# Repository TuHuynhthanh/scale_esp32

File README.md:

# scale_esp32
esp32 read information from electronic scale.
- USB HID CP2110
- USB COM debug ESP32 via terminal

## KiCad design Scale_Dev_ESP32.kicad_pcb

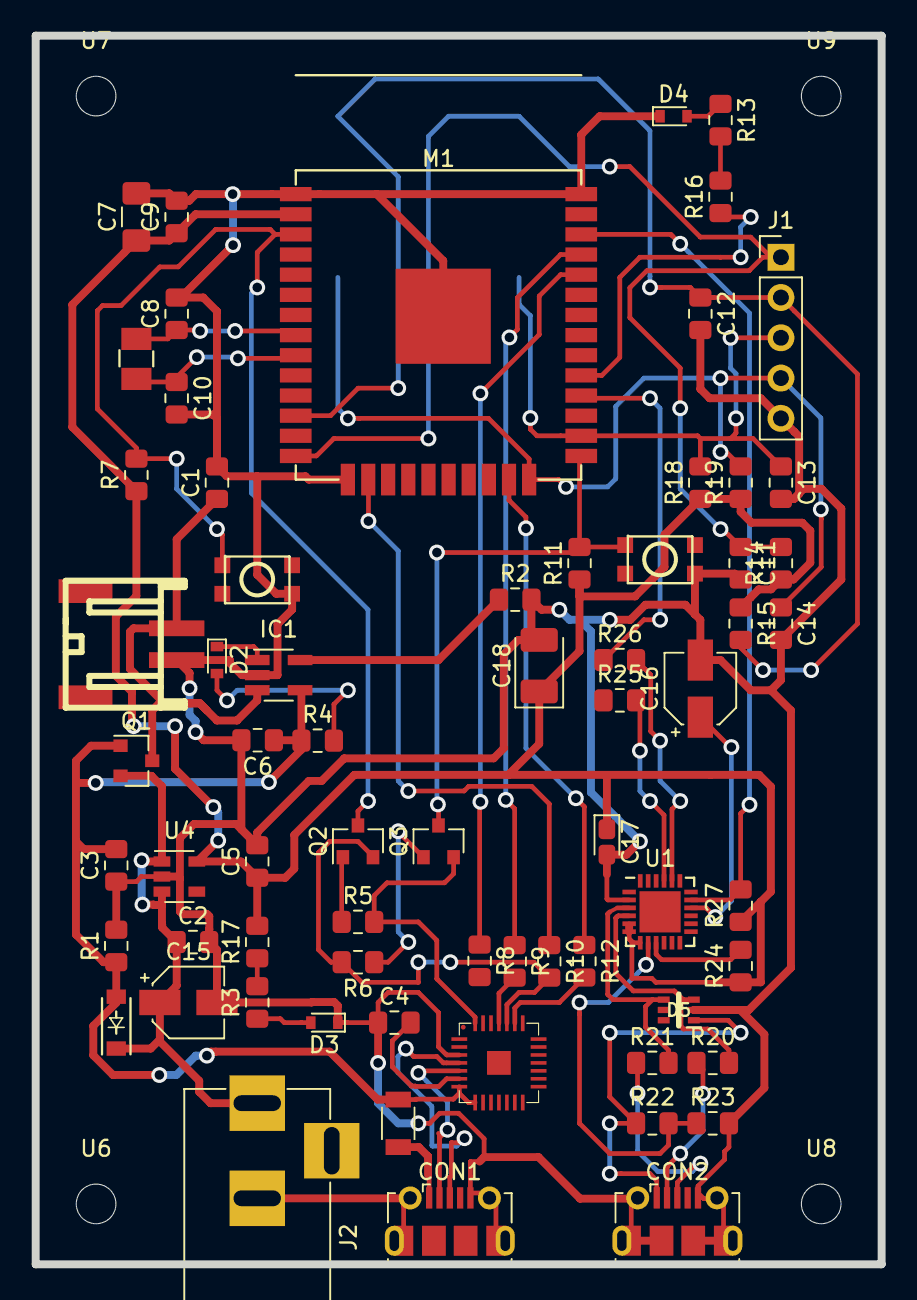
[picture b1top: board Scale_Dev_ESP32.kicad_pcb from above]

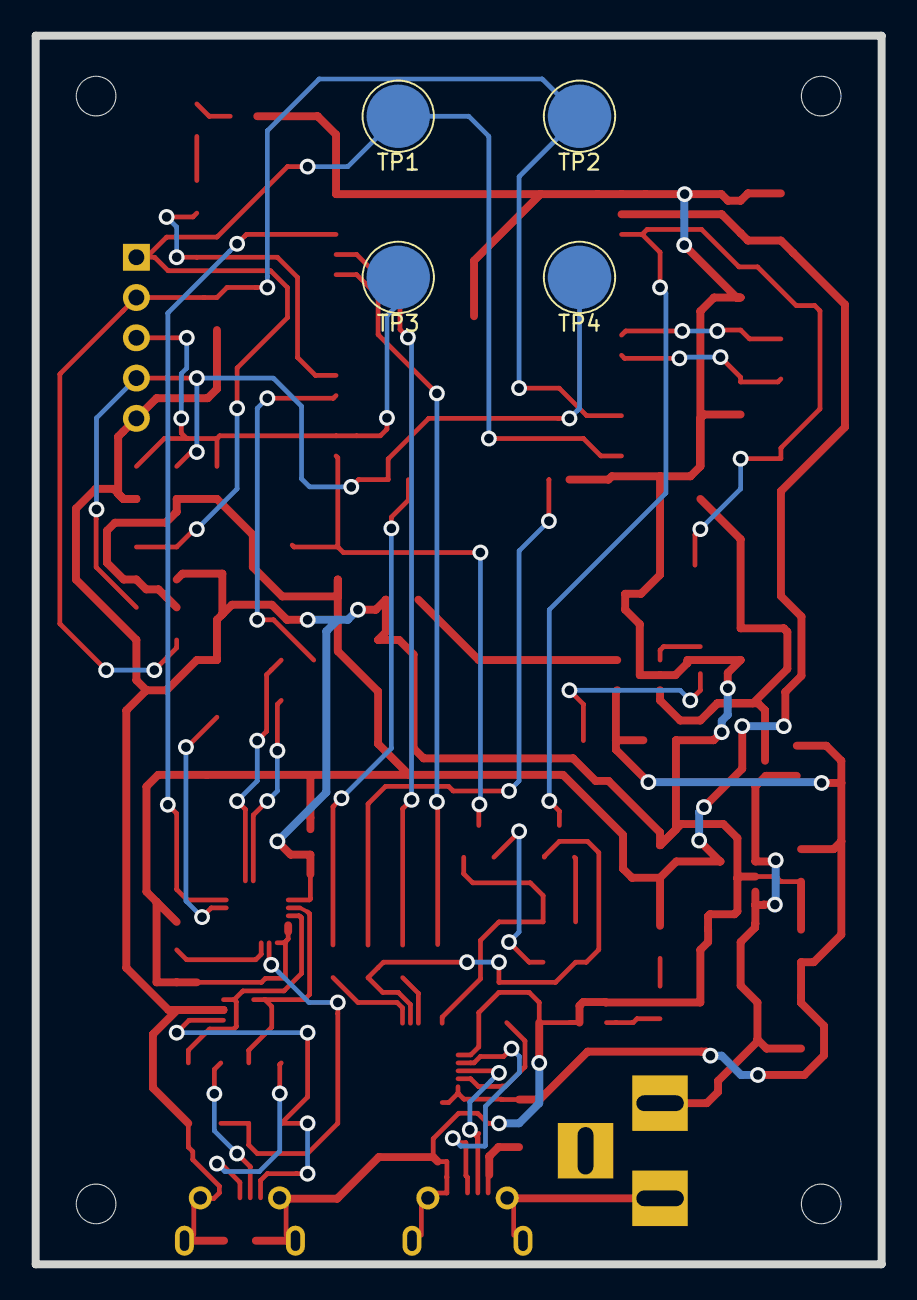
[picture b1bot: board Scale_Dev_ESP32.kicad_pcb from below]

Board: 2 copper layers, 53.3 x 77.5 mm, 75 parts (4 on the bottom side), 47 nets.

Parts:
C1, C6: 4.7uF; C_0805_2012Metric_Pad1.15x1.40mm_HandSolder
C2: 1uF; C_0805_2012Metric_Pad1.15x1.40mm_HandSolder
C3, C4: 0.1uF; C_0805_2012Metric_Pad1.15x1.40mm_HandSolder
C5: 2.2uF; C_0805_2012Metric_Pad1.15x1.40mm_HandSolder
C7: 100uF; C_1206_3216Metric_Pad1.42x1.75mm_HandSolder
C8, C10: 15pF; C_0805_2012Metric_Pad1.15x1.40mm_HandSolder
C9: 100nF; C_0805_2012Metric_Pad1.15x1.40mm_HandSolder
C11, C12, C13, C14: C; C_0805_2012Metric_Pad1.15x1.40mm_HandSolder
C15: 10uF; CP_Elec_4x3
C16: 4.7uF; CP_Elec_4x3
C17: 0.1uF; CP_EIA-1608-10_AVX-L_Pad1.25x1.05mm_HandSolder
C18: 1uF; CP_EIA-3528-12_Kemet-T_Pad1.50x2.35mm_HandSolder
CON1, CON2: USB_B_Micro; USB_Micro-B_Molex-105017-0001
D1: BAT20J; SOD-80_diode_1
D2: Yellow; D_0603
D3: LED; D_0603
D4: Blue; D_0603
D5: SMF05C; SC-70-6
F1: 500mA; Fuse_500mA
IC1: MCP73831; SOT-23-5_HandSoldering
J1: BUTTON; PinHeader_1x05_P2.54mm_Vertical
J2: Jack-DC; BARREL_JACK
M1: ESP-WROOM-32; ESP-32S
P1: LIPO; JST_SMD
Q1: IRLML5203; SOT-23
Q2, Q3: S8050; SOT-23
R1: 100K; R_0805_2012Metric_Pad1.15x1.40mm_HandSolder
R2: 2K; R_0805_2012Metric_Pad1.15x1.40mm_HandSolder
R3, R4: 1K; R_0805_2012Metric_Pad1.15x1.40mm_HandSolder
R5, R6: 12K; R_0805_2012Metric_Pad1.15x1.40mm_HandSolder
R7, R11, R14, R18, R19: 10K; R_0805_2012Metric_Pad1.15x1.40mm_HandSolder
R8, R9, R10, R12, R16, R17: 0E; R_0805_2012Metric_Pad1.15x1.40mm_HandSolder
R13: 330E; R_0805_2012Metric_Pad1.15x1.40mm_HandSolder
R15: 10k; R_0805_2012Metric_Pad1.15x1.40mm_HandSolder
R20, R21, R25, R26: 22R; R_0805_2012Metric_Pad1.15x1.40mm_HandSolder
R22: 47K; R_0805_2012Metric_Pad1.15x1.40mm_HandSolder
R23: 24K; R_0805_2012Metric_Pad1.15x1.40mm_HandSolder
R24: 4K7; R_0805_2012Metric_Pad1.15x1.40mm_HandSolder
R27: R; R_0805_2012Metric_Pad1.15x1.40mm_HandSolder
SW1, SW2: SW_PUSH; smd_push2_New
TP1, TP2, TP3, TP4: TestPoint; TestPoint_Pad_D4.0mm
U1: CP2110; QFN-24-1EP_4x4mm_Pitch0.5mm
U4: AP2112K; SOT-23-5
U5: CP2102; cp2102_xl2
U6, U7, U8, U9: MountingHole; MountingHole_2.5mm
Y1: 32.768KHz RTC Crystal; SMD_RTC_Crstl

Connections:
+3V3: C5.1, C7.1, C9.1, C17.1, C18.1, M1.2, R7.1, R11.1, R14.1, R15.1, R17.2, R18.1, R19.1, R24.1, R27.1, U1.5, U1.6, U1.7, U4.5
+5V: C2.1, C15.1, D1.1, J2.1, Q1.2, U4.1, U4.3
+BATT: C1.1, IC1.3, P1.1, Q1.3
/BUT0: C11.1, J1.1, M1.14, R14.2, TP1.1
/BUT1: C12.1, J1.2, M1.12, R15.2, TP2.1
/BUT2: C13.1, J1.3, M1.26, R18.2, TP3.1
/BUT3: C14.1, J1.4, M1.24, R19.2, TP4.1
/CP2110_SUS: M1.36, R27.2, U1.17
/DTR: Q3.2, R5.2
/EN: M1.3, Q2.3, R7.2, SW1.1
/IO0: M1.25, Q3.3, R11.2, SW2.1
/IO5: M1.29, R16.1
/IO13: M1.16, R10.1
/IO15: M1.23, R12.1
/IO32: C8.1, M1.8, Y1.1
/IO33: C10.1, M1.9, Y1.2
/RTS: Q2.2, R6.2, R10.2, U5.24
/RXD0: M1.34, R8.1
/TXD0: M1.35, R9.1
/U2_TX: M1.28, R26.1
/USB_N: D5.3, R20.2, U1.4
/USB_P: D5.4, R21.2, U1.3
/VBUS: R22.2, R23.1, U1.8
GND: C1.2, C2.2, C3.1, C4.1, C5.2, C6.2, C7.2, C8.2, C9.2, C10.2, C11.2, C12.2, C13.2, C14.2, C15.2, C16.2, C17.2, C18.2, CON1.5, CON1.6, CON2.5, CON2.6, D3.1, D4.1, D5.2, IC1.2, J1.5, J2.2, M1.1, M1.15, M1.38, P1.2, R1.2, R2.2, R23.2, SW1.2, SW2.2, U1.2, U4.2, U5.3
unnamed: C4.2, U5.6
unnamed: C16.1, U1.16
unnamed: CON1.1, F1.2
unnamed: CON1.2, U5.5
unnamed: CON1.3, U5.4
unnamed: CON2.1, D5.1, R22.1
unnamed: CON2.2, R20.1
unnamed: CON2.3, R21.1
unnamed: D2.1, IC1.1
unnamed: D2.2, R4.2
unnamed: D3.2, R3.1
unnamed: D4.2, R13.1
unnamed: IC1.5, R2.1
unnamed: Q2.1, R5.1
unnamed: Q3.1, R6.1
unnamed: R9.2, U5.25
unnamed: R12.2, U5.23
unnamed: R13.2, R16.2
unnamed: R3.2, R17.1
unnamed: R24.2, U1.9
unnamed: R25.2, U1.21
unnamed: R26.2, U1.20
VCC: C3.2, C6.1, D1.2, F1.1, IC1.4, Q1.1, R1.1, R4.1, U5.7, U5.8

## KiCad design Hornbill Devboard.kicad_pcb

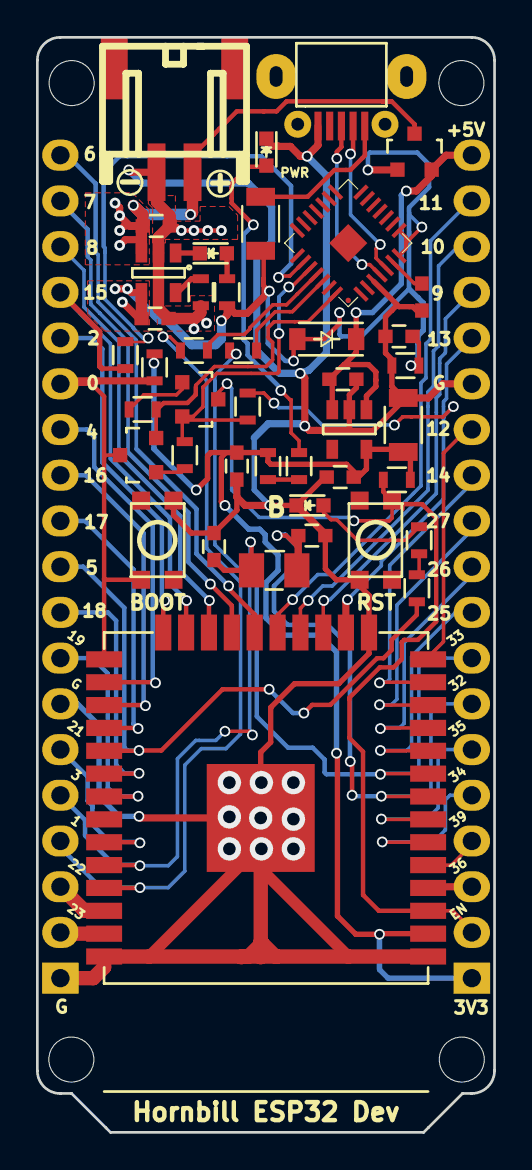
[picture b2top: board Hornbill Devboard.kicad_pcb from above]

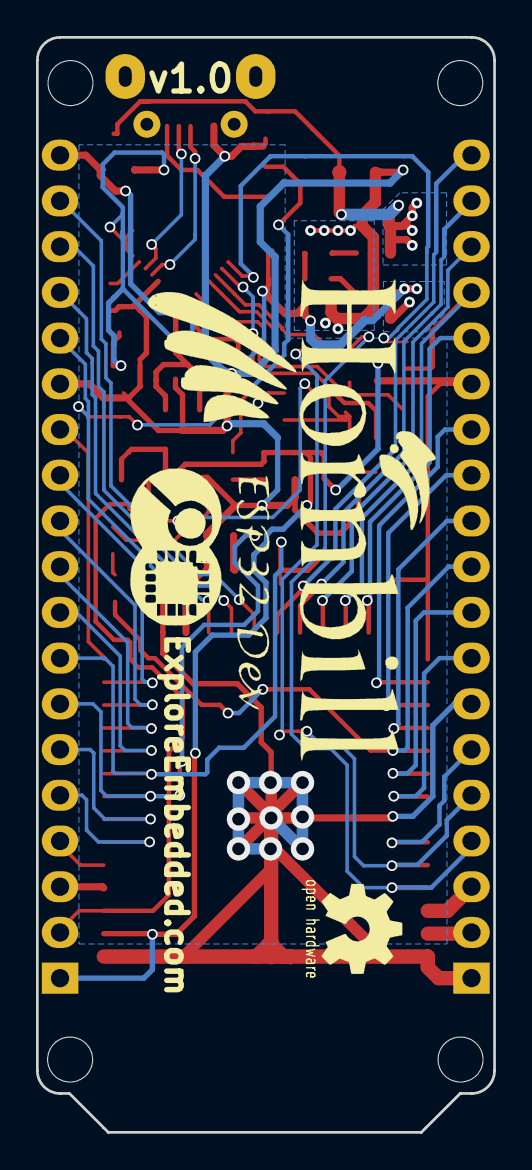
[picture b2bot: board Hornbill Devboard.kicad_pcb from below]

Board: 2 copper layers, 25.4 x 60.8 mm, 51 parts (3 on the bottom side), 56 nets.

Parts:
C1, C6: 4.7uF; C_0603
C2: 1uF; C_0603
C3, C4: 0.1uF; C_0603
C5: 2.2uF; C_0603
C7: 100uF; C_1206
C8, C10: 15pF; C_0603
C9: 100nF; C_0603
CON1: USB-MINI-B; USB_Micro-B_SMD_NEW_1
D1: BAT20J; SOD-80_diode
D2: Yellow; LED-0603
D3: LED; LED-0603
D4: Blue; LED-0603
F1: 500mA; Fuse_500mA
IC1: MCP73831; SOT-23-5
M1: ESP-WROOM-32; ESP-32S
P1: LIPO; JST_SMD
P2, P3: CONN_01X19; Pin_Header_Straight_1x19
Q1: IRLML5203; SOT-23
Q2, Q3: S8050; SOT-23
R1: 100K; R_0603
R2: 2K; R_0603
R3, R4: 1K; R_0603
R5, R6: 12K; R_0603
R7, R11: 10K; R_0603
R8, R9, R10, R12, R16, R17: 0E; R_0603
R13: 330E; R_0603
SW1, SW2: SW_PUSH; smd_push2_New
U1: OSH_Symbol; Logo_silk_OSHW_6x6mm
U2: EE_Logo; Hornbill_ESP32_Dev
U3: EE_Logo; Logo_8
U4: AP2112K; SOT-23-5
U5: CP2102; cp2102_xl2
U6, U7, U8, U9: MountingHole; MountingHole_2-5mm
Y1: 32.768KHz RTC Crystal; SMD_RTC_Crstl

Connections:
+3V3: C5.1, C7.1, C9.1, M1.2, P2.1, R7.1, R11.1, R17.2, U4.5
+5V: C2.1, D1.1, P2.19, Q1.2, U4.1, U4.3
+BATT: C1.1, IC1.3, P1.1, Q1.3
/CLK: M1.20, P3.19
/CMD: M1.19, P2.18
/DTR: Q3.2, R5.2, U5.28
/EN: M1.3, P2.2, Q2.3, R7.2, SW1.1
/IO0: M1.25, P3.14, Q3.3, R11.2, SW2.1
/IO2: M1.24, P3.15
/IO4: M1.26, P3.13
/IO5: M1.29, P3.10, R16.1
/IO12: M1.14, P2.13
/IO13: M1.16, P2.15, R10.1
/IO14: M1.13, P2.12
/IO15: M1.23, P3.16, R12.1
/IO16: M1.27, P3.12
/IO17: M1.28, P3.11
/IO18: M1.30, P3.9
/IO19: M1.31, P3.8
/IO21: M1.33, P3.6
/IO22: M1.36, P3.3
/IO23: M1.37, P3.2
/IO25: M1.10, P2.9
/IO26: M1.11, P2.10
/IO27: M1.12, P2.11
/IO32: C8.1, M1.8, P2.7, Y1.1
/IO33: C10.1, M1.9, P2.8, Y1.2
/IO34: M1.6, P2.5
/IO35: M1.7, P2.6
/RTS: Q2.2, R6.2, R10.2, U5.24
/RXD0: M1.34, P3.5, R8.1
/SD0: M1.21, P3.18
/SD1: M1.22, P3.17
/SD2: M1.17, P2.16
/SD3: M1.18, P2.17
/SENSOR_VN: M1.5, P2.4
/SENSOR_VP: M1.4, P2.3
/TXD0: M1.35, P3.4, R9.1
GND: C1.2, C2.2, C3.1, C4.1, C5.2, C6.2, C7.2, C8.2, C9.2, C10.2, CON1.5, D3.1, D4.1, IC1.2, M1.1, M1.15, M1.38, P1.2, P2.14, P3.1, P3.7, R1.2, R2.2, SW1.2, SW2.2, U4.2, U5.3
unnamed: C4.2, U5.6
unnamed: CON1.1, F1.2
unnamed: CON1.2, U5.5
unnamed: CON1.3, U5.4
unnamed: D2.1, IC1.1
unnamed: D2.2, R4.2
unnamed: D3.2, R3.1
unnamed: D4.2, R13.1
unnamed: IC1.5, R2.1
unnamed: Q2.1, R5.1
unnamed: Q3.1, R6.1
unnamed: R8.2, U5.26
unnamed: R9.2, U5.25
unnamed: R12.2, U5.23
unnamed: R13.2, R16.2
unnamed: R3.2, R17.1
VCC: C3.2, C6.1, D1.2, F1.1, IC1.4, Q1.1, R1.1, R4.1, U5.7, U5.8

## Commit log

2018-10-16 add scale project
2018-10-16 update lib
2018-10-16 update 2
2018-10-17 update pcb footprint
2018-10-17 rename kicad pcb file
2018-10-17 place pcb items
2018-10-17 update pcb wire
2018-10-18 update pcb route
2018-10-19 update route from linux machine
2018-10-20 update route ubuntu
